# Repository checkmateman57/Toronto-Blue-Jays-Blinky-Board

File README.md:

# Toronto Blue Jays Blinky Board
I created a blinky board as per the starter guide's manual, and have the custom shape of the Toronto Blue Jays logo. I chose this design because I really enjoyed their playoff run last year and wanted to honour them, which is why I have pictures of them being ALCS champs on the silkscreen.

# Components

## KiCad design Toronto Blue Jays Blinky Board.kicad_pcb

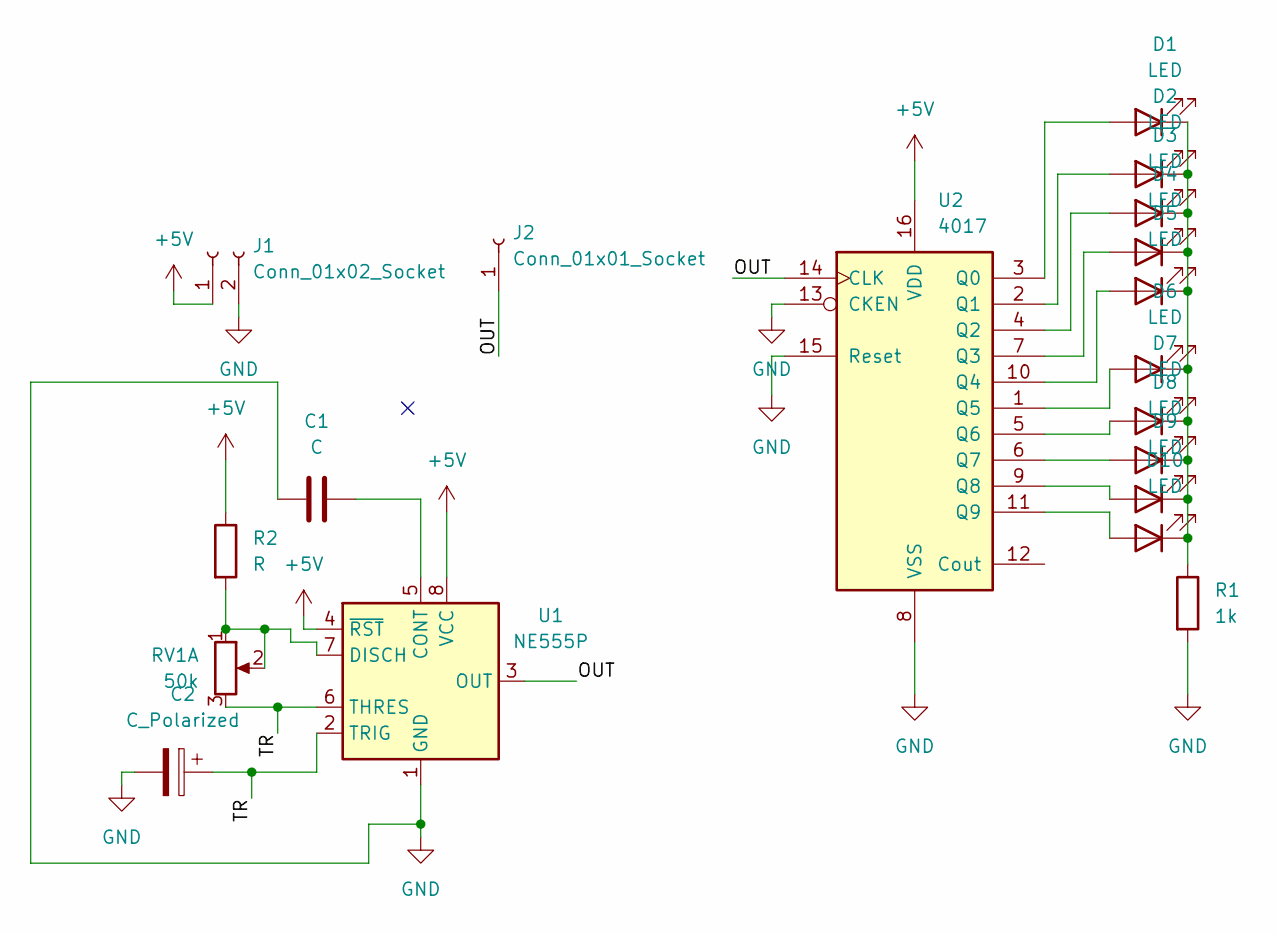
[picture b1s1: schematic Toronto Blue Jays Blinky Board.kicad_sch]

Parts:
C1: C; CP_Radial_D5.0mm_P2.00mm
C2: C_Polarized; C_Disc_D7.5mm_W2.5mm_P5.00mm
D1, D2, D3, D4, D5, D6, D7, D8, D9, D10: LED; LED_D3.0mm
J1: Conn_01x02_Socket; PinHeader_1x02_P2.54mm_Vertical
J2: Conn_01x01_Socket; PinHeader_1x01_P2.54mm_Vertical
R1: 1k; R_Axial_DIN0207_L6.3mm_D2.5mm_P7.62mm_Horizontal
R2: R; R_Axial_DIN0207_L6.3mm_D2.5mm_P7.62mm_Horizontal
RV1: 50k; Potentiometer_Vishay_T93YA_Vertical
U1: NE555P; DIP-8_W7.62mm
U2: 4017; N16

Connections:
+5V: J1.1, R2.1, U1.4 (~RST), U1.8 (VCC), U2.16 (VDD)
/OUT: J2.1, U1.3 (OUT), U2.14 (CLK)
/TR: C2.1, RV1.3, U1.2 (TRIG), U1.6 (THRES)
GND: C1.2, C2.2, J1.2, R1.2, U1.1 (GND), U2.8 (VSS), U2.13 (CKEN), U2.15 (Reset)
unnamed: D1.2 (A), U2.3 (Q0)
unnamed: D1.1 (K), D2.1 (K), D3.1 (K), D4.1 (K), D5.1 (K), D6.1 (K), D7.1 (K), D8.1 (K), D9.1 (K), D10.1 (K), R1.1
unnamed: D2.2 (A), U2.2 (Q1)
unnamed: D3.2 (A), U2.4 (Q2)
unnamed: D4.2 (A), U2.7 (Q3)
unnamed: D5.2 (A), U2.10 (Q4)
unnamed: D6.2 (A), U2.1 (Q5)
unnamed: D7.2 (A), U2.5 (Q6)
unnamed: D8.2 (A), U2.6 (Q7)
unnamed: D9.2 (A), U2.9 (Q8)
unnamed: D10.2 (A), U2.11 (Q9)
unnamed: C1.1, U1.5 (CONT)
unnamed: R2.2, RV1.1, RV1.2, U1.7 (DISCH)

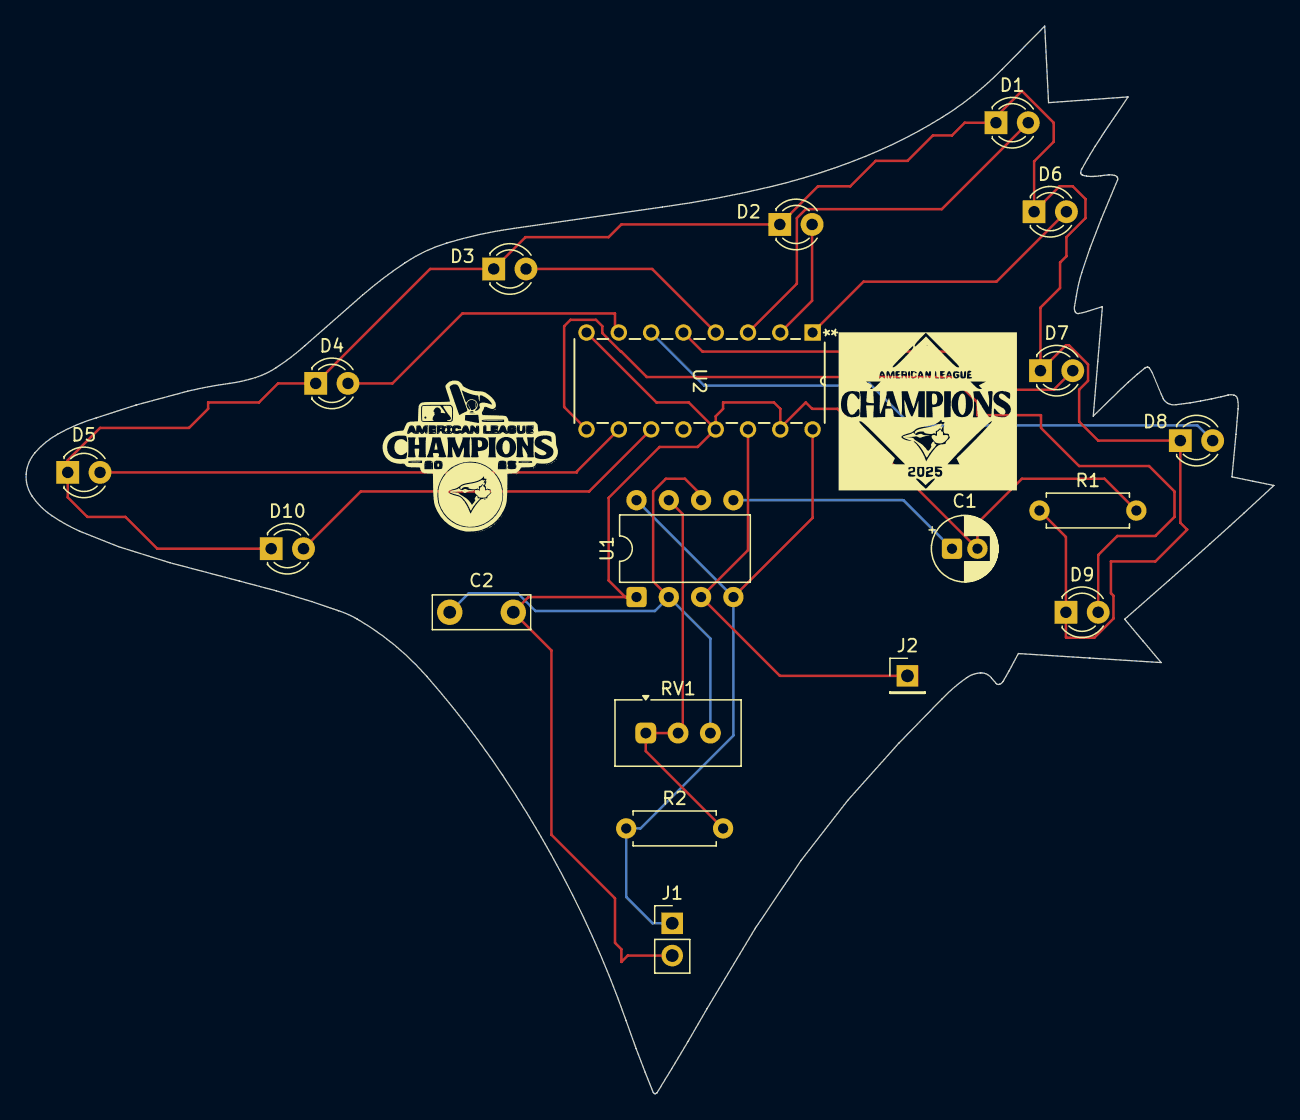
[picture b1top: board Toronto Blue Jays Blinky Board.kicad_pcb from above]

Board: 2 copper layers, 98.1 x 84.0 mm, 19 parts (0 on the bottom side), 17 nets.
